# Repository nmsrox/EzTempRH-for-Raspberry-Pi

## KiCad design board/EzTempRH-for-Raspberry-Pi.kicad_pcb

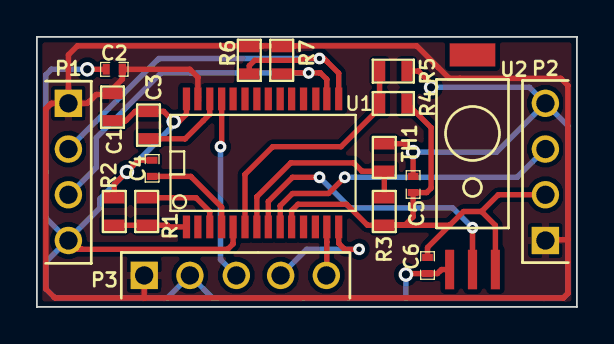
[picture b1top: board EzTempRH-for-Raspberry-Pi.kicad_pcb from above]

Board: 2 copper layers, 30.0 x 15.0 mm, 19 parts (0 on the bottom side), 16 nets.

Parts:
C1, C3: 1uF; SMD_0603
C2, C4: .1uF; SMD_0402
C5, C6: C; SMD_0402
P1, P2: CONN_4; PIN_4POS_1ROW_PTH_RA_2.54MM
P3: CONN_5; PIN_5POS_1ROW_PTH_RA_2.54MM
R1: 1.5K; SMD_0603
R2: 680; SMD_0603
R3, R4, R5: 10K; SMD_0603
R6, R7: 5.6k; SMD_0603
TH1: THERMISTOR; SMD_0603
U1: CY8C4100-28SSOP; CY8C4xxx-28SSOP
U2: HIH5030

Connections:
/ADC_BY: C4.1, U1.4
/ADC_IN: R1.2, R2.1, U1.1
/EN: C5.1, C6.1, P2.2, R3.1, R4.1, U1.10, U2.1
/EXT_T: P2.3, U1.9
/OA_O: R1.1, U1.3
/RH_T: U1.8, U2.2
/RX: P1.2, R7.2, U1.15
/SWDCK: P3.4, U1.14
/SWDIO: P3.5, U1.13
/TH_T: R3.2, TH1.1, U1.7
/TX: P1.3, R6.2, U1.16
/VDD_T: R4.2, R5.1, U1.6
/Vccd: C3.1, U1.26
/Vddd: C1.1, C2.1, P1.1, P2.1, P3.1, R6.1, R7.1, U1.27
/Vss: C1.2, C2.2, C3.2, C4.2, C5.2, C6.2, P1.4, P2.4, P3.2, R2.2, R5.2, TH1.2, U1.5, U1.28, U2.3
/XRES: P3.3, U1.25

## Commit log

2014-09-12 Schematic draft
2014-09-12 Added schematic on PDF
2014-09-18 Updated schematic
    - Use opamp to buffer signals.
    - Added 3.3v to 1.024v voltage divider to use internal reference.
    - Added voltage reading circuit
2014-09-23 First prototype
    New schematic, now using the 1.024v reference and OpAmp buffering. Added
    resistors for I2C option. First layout.
2014-09-23 Added BOM
2014-10-29 Silkscreen text and programming fix
    Added silkscreen text on pins.
    Fix a minor issue with the programming connector and pins position.
2014-10-29 Firmware and test script
    First commit of firmware (bootloader and application).
    First commit of a test script for Raspberry Pi.
2014-10-29 Unsaved schematic
2014-11-04 DFM correction
    Corrected R6 and R7 for manufacturing
2014-12-17 Firmware RC1
2015-01-21 Updated example, added datasheet
2015-02-23 New chip CY8C4124PVI-432
    Target device updated to CY8C4124PVI-432
    PSoC Creator components updated
    Built with ARM_GCC_484
    FW Revision updated to #2
2015-04-10 Generic calibration
    2-point averaged calibration of temperature.
2015-04-10 Updated gitignore
    bug on .gitignore commited compilation temporary files.
2015-04-10 Calibrated
    averaged 2-point calibration of temperature
